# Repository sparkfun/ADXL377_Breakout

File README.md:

ADXL377 Breakout
================

[   
*Triple Axis Accelerometer Breakout-ADXL377 (SEN-12803)*](https://www.sparkfun.com/products/12803)

A Breakout Board for the ADXL377 Low Power 3-Axis ±200g Accelerometer with Analog Output.

Repository Contents
-------------------
* **/Hardware** - All Eagle design files (.brd, .sch)
* **/Production** - Test bed files and production panel files
* **/Firmware** - All Arduino sketches for this product

License Information
-------------------
The hardware is released under [Creative Commons ShareAlike 4.0 International](https://creativecommons.org/licenses/by-sa/4.0/).

Distributed as-is; no warranty is given.

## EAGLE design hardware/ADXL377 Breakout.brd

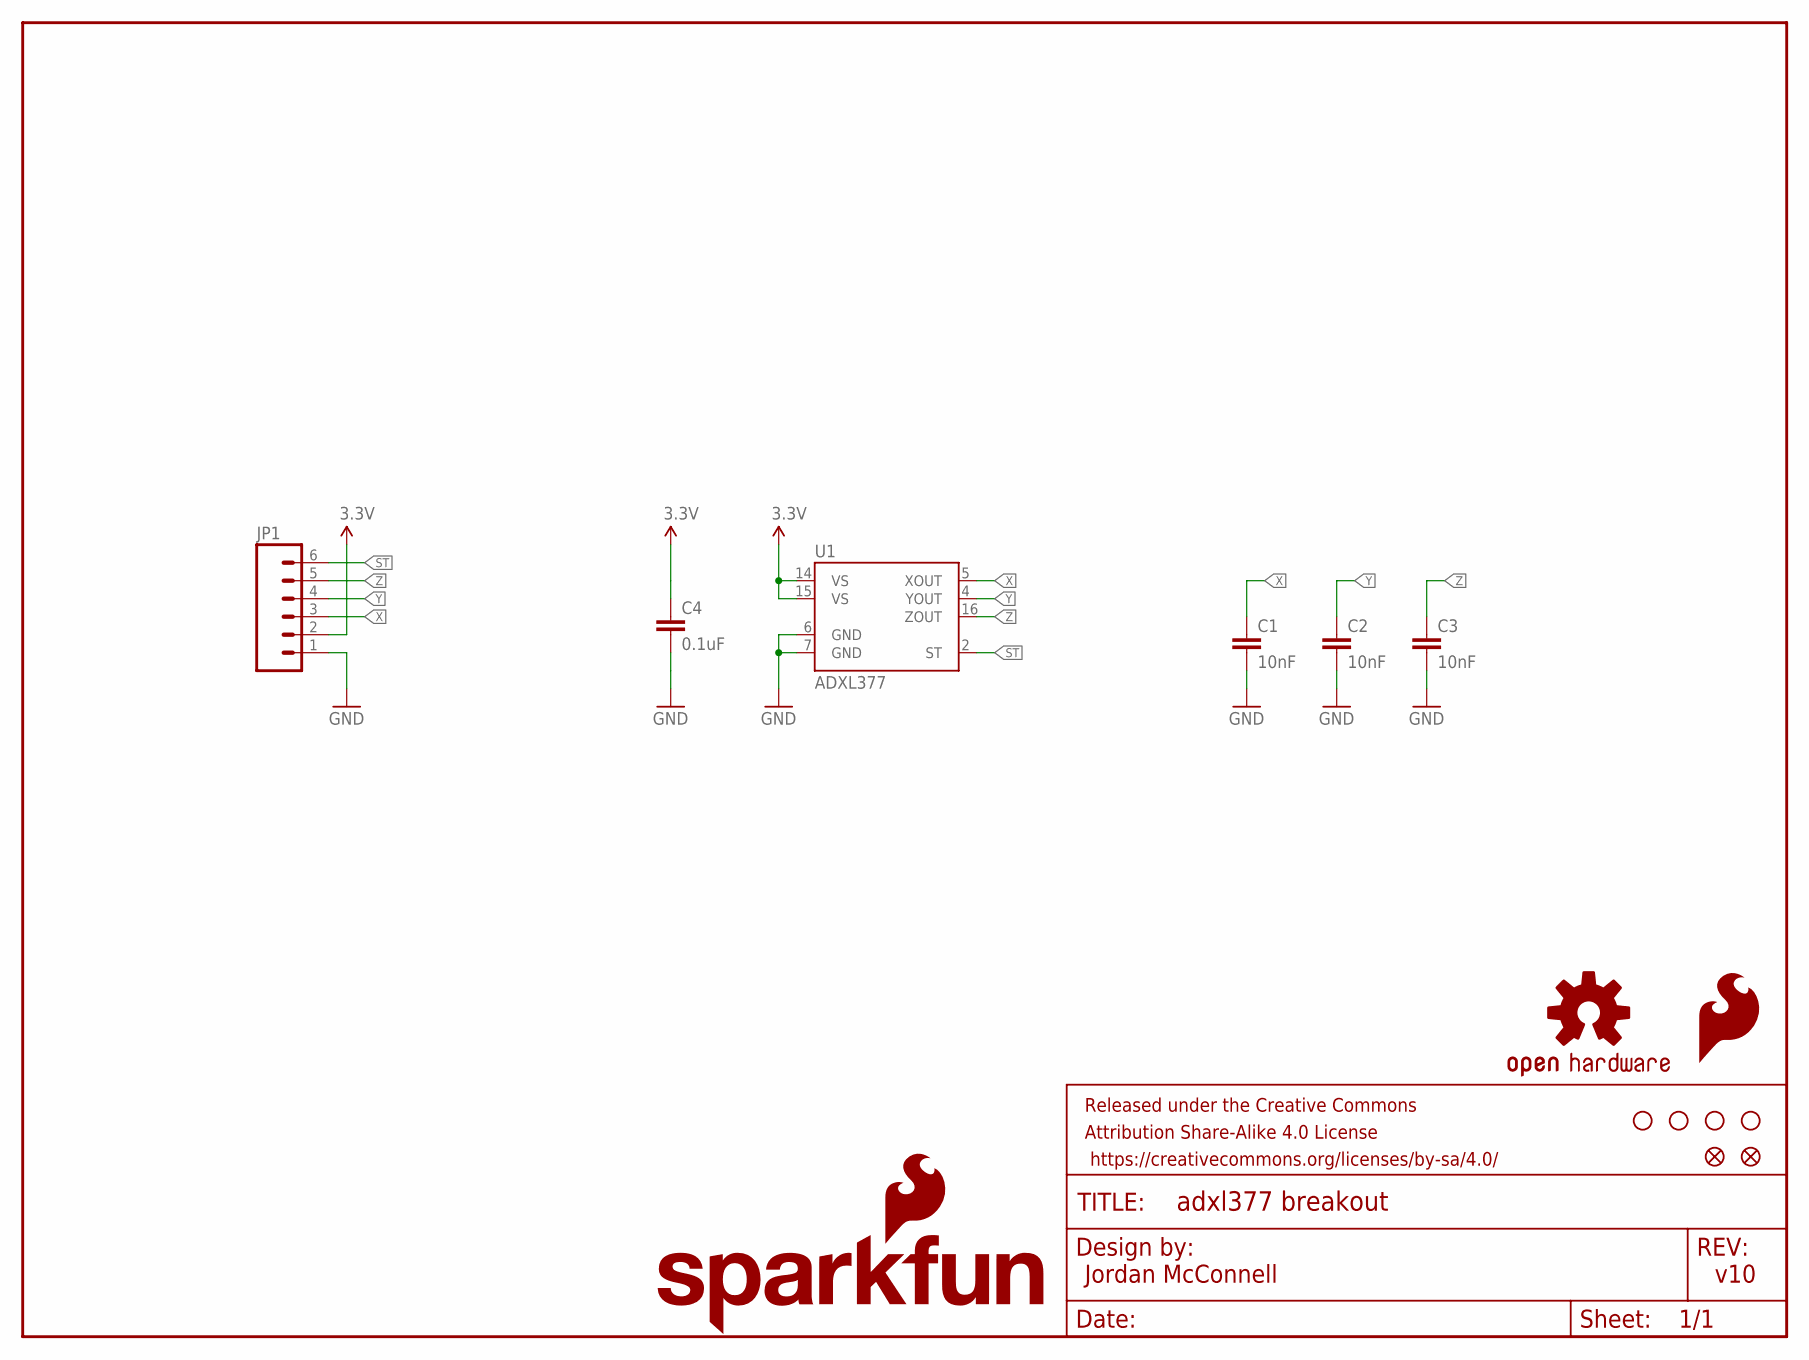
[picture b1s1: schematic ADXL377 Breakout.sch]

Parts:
C1, C2, C3: 10nF; 0603-CAP
C4: 0.1uF; 0603-CAP
FID1, FID2: FIDUCIAL1X2; FIDUCIAL-1X2
FRAME1: FRAME-LETTER; CREATIVE_COMMONS
JP1: M06SIP; 1X06
LOGO1: SFE_LOGO_FLAME.1_INCH; SFE_LOGO_FLAME_.1
LOGO2: OSHW-LOGOS; OSHW-LOGO-S
LOGO5: SFE_LOGO_NAME_FLAME.1_INCH; SFE_LOGO_NAME_FLAME_.1
STANDOFF1, STANDOFF2, STANDOFF3, STANDOFF4: STAND-OFF
U1: ADXL377; LFCSP_LQ-16

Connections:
3.3V: C4.1, JP1.2, U1.14 (VS), U1.15 (VS)
GND: C1.2, C2.2, C3.2, C4.2, JP1.1, U1.6 (GND), U1.7 (GND)
ST: JP1.6, U1.2 (ST)
X: C1.1, JP1.3, U1.5 (XOUT)
Y: C2.1, JP1.4, U1.4 (YOUT)
Z: C3.1, JP1.5, U1.16 (ZOUT)

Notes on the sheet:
Jordan McConnell
v10

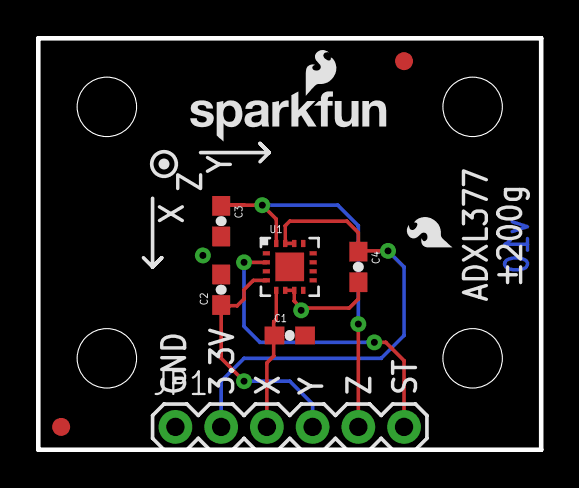
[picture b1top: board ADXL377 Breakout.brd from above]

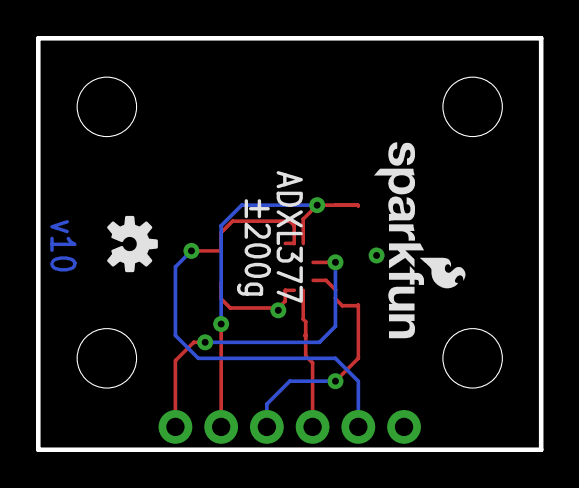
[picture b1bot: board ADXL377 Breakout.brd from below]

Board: 2 copper layers, 27.9 x 22.9 mm, 17 parts (2 on the bottom side), 6 nets.

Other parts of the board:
LOGO3: SFE_LOGO_NAME_FLAME.1_INCH; SFE_LOGO_NAME_FLAME_.1

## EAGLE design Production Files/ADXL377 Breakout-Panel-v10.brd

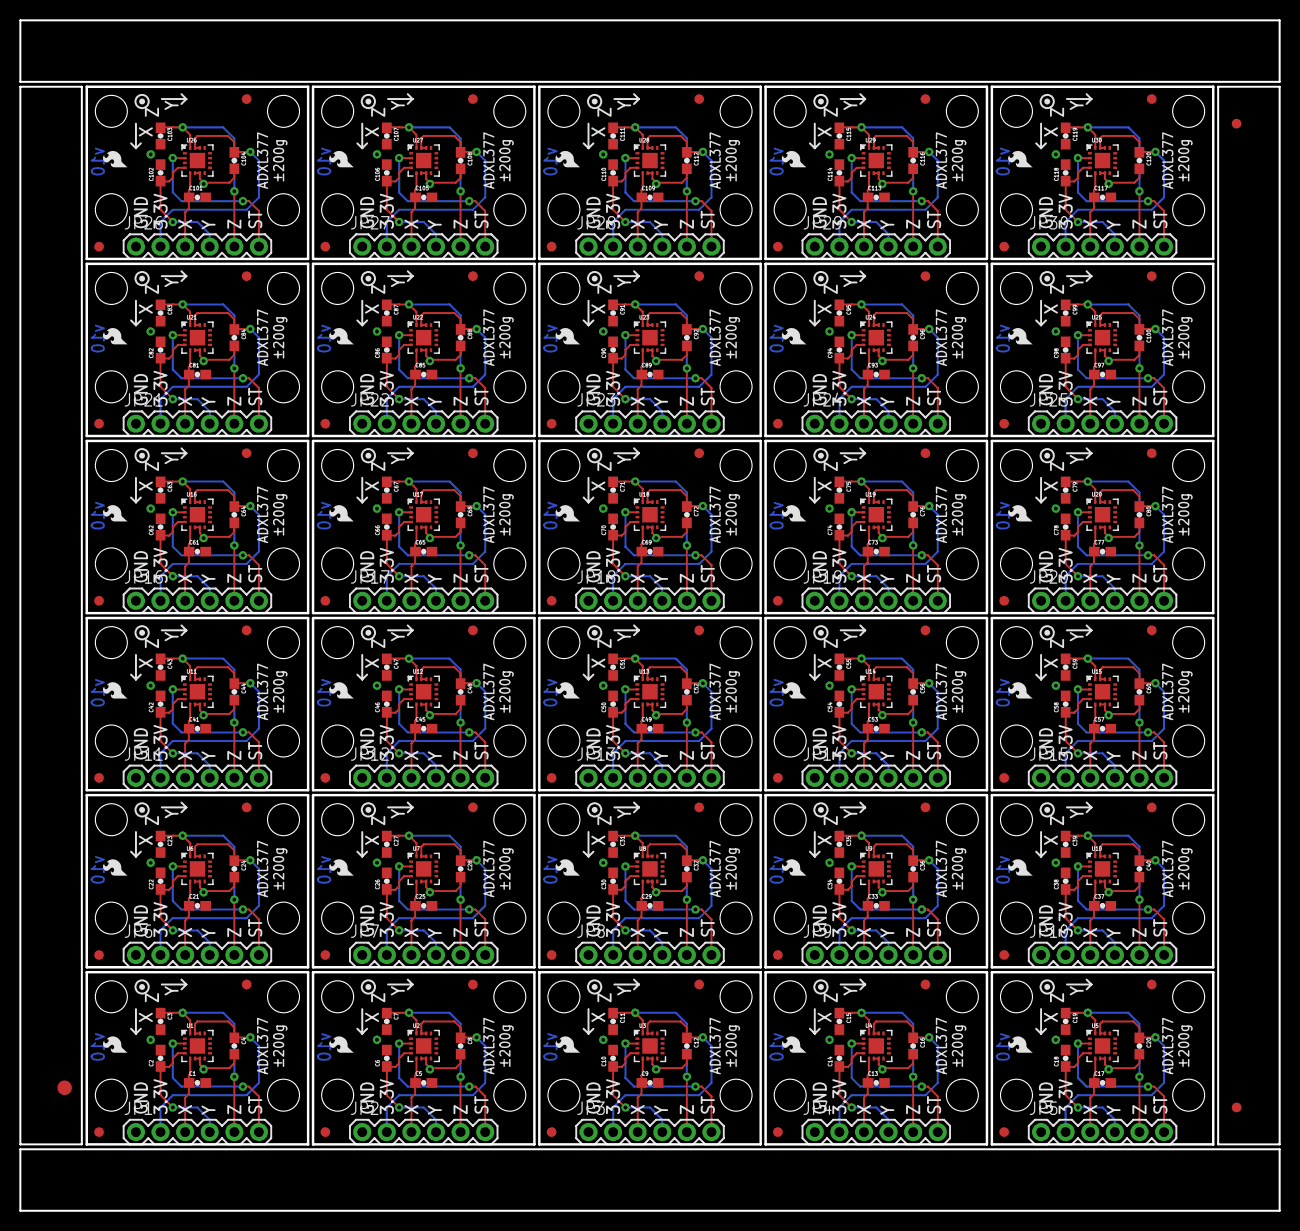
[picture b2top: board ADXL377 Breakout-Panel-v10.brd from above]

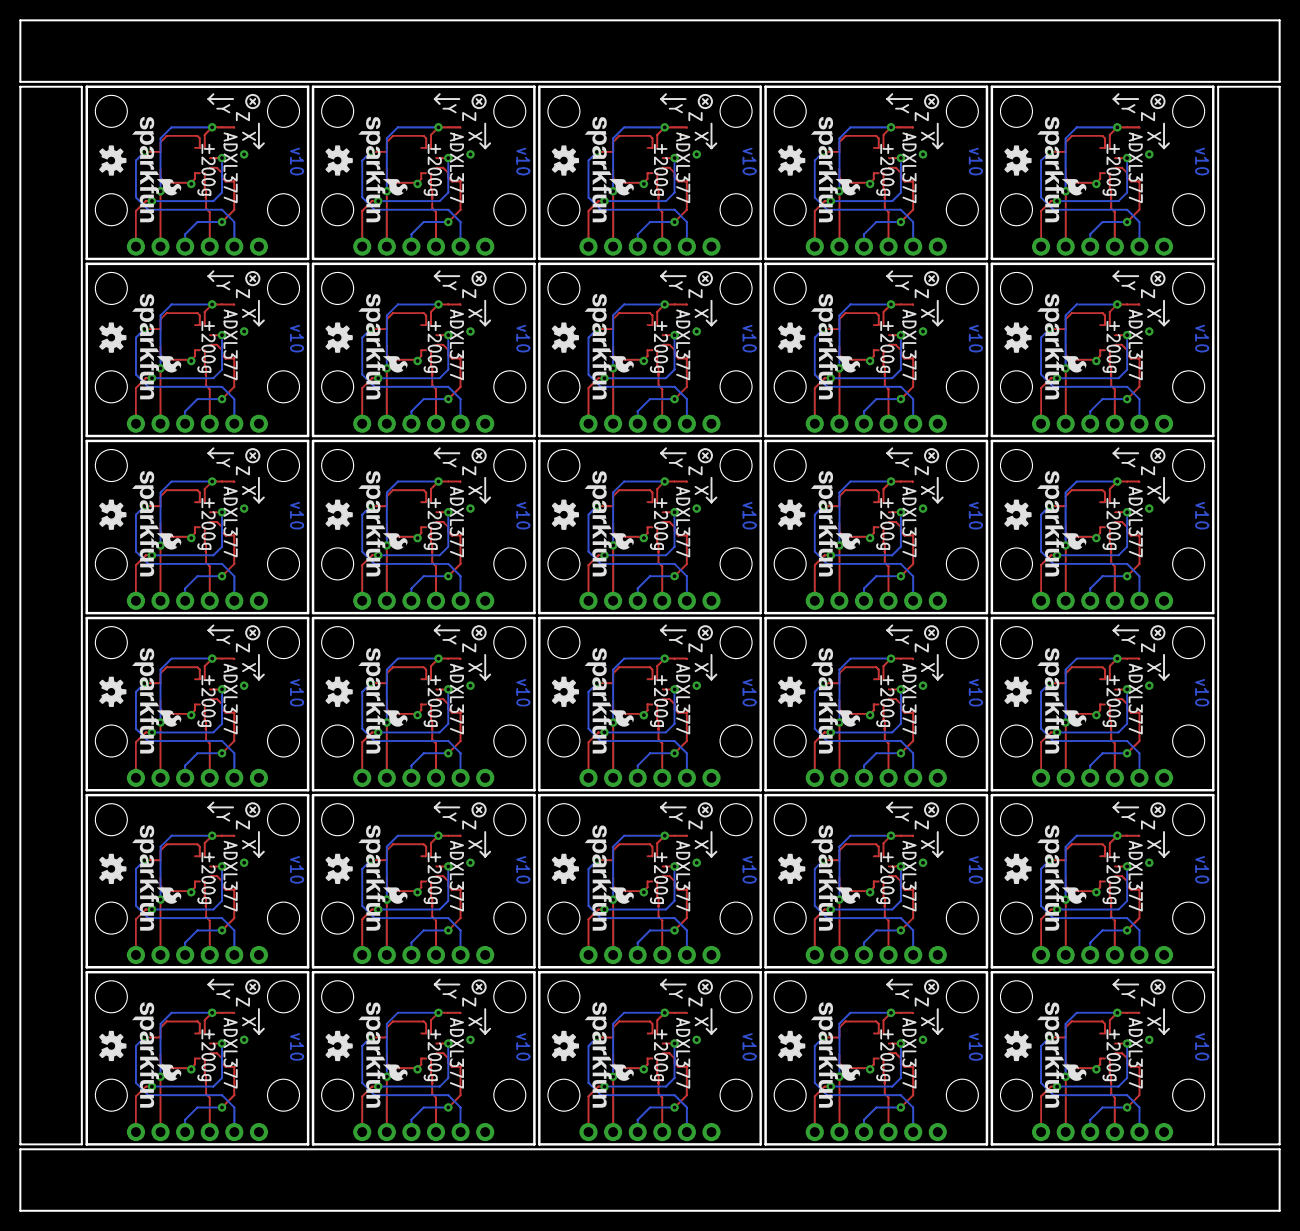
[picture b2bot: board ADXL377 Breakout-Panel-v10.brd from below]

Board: 2 copper layers, 130.0 x 122.9 mm, 453 parts (60 on the bottom side), 180 nets.

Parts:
C1, C2, C3, C5, C6, C7, C9, C10, C11, C13, C14, C15, C17, C18, C19, C21, C22, C23, C25, C26, C27, C29, C30, C31, C33, C34, C35, C37, C38, C39, C41, C42, C43, C45, C46, C47, C49, C50, C51, C53, C54, C55, C57, C58, C59, C61, C62, C63, C65, C66, C67, C69, C70, C71, C73, C74, C75, C77, C78, C79, C81, C82, C83, C85, C86, C87, C89, C90, C91, C93, C94, C95, C97, C98, C99, C101, C102, C103, C105, C106, C107, C109, C110, C111, C113, C114, C115, C117, C118, C119: 10nF; 0603-CAP
C4, C8, C12, C16, C20, C24, C28, C32, C36, C40, C44, C48, C52, C56, C60, C64, C68, C72, C76, C80, C84, C88, C92, C96, C100, C104, C108, C112, C116, C120: 0.1uF; 0603-CAP
E$1: FIDUCIAL-1.5X3
E$4, E$6: FIDUCIAL-1X2
FID1, FID2, FID3, FID4, FID5, FID6, FID7, FID8, FID9, FID10, FID11, FID12, FID13, FID14, FID15, FID16, FID17, FID18, FID19, FID20, FID21, FID22, FID23, FID24, FID25, FID26, FID27, FID28, FID29, FID30, FID31, FID32, FID33, FID34, FID35, FID36, FID37, FID38, FID39, FID40, FID41, FID42, FID43, FID44, FID45, FID46, FID47, FID48, FID49, FID50, FID51, FID52, FID53, FID54, FID55, FID56, FID57, FID58, FID59, FID60: FIDUCIAL1X2; FIDUCIAL-1X2
JP1, JP2, JP3, JP4, JP5, JP6, JP7, JP8, JP9, JP10, JP11, JP12, JP13, JP14, JP15, JP16, JP17, JP18, JP19, JP20, JP21, JP22, JP23, JP24, JP25, JP26, JP27, JP28, JP29, JP30: 1X06
LOGO1, LOGO4, LOGO7, LOGO10, LOGO13, LOGO16, LOGO19, LOGO22, LOGO25, LOGO28, LOGO31, LOGO34, LOGO37, LOGO40, LOGO43, LOGO46, LOGO49, LOGO52, LOGO55, LOGO58, LOGO61, LOGO64, LOGO67, LOGO70, LOGO73, LOGO76, LOGO79, LOGO82, LOGO85, LOGO88: SFE_LOGO_FLAME.1_INCH; SFE_LOGO_FLAME_.1
LOGO2, LOGO5, LOGO8, LOGO11, LOGO14, LOGO17, LOGO20, LOGO23, LOGO26, LOGO29, LOGO32, LOGO35, LOGO38, LOGO41, LOGO44, LOGO47, LOGO50, LOGO53, LOGO56, LOGO59, LOGO62, LOGO65, LOGO68, LOGO71, LOGO74, LOGO77, LOGO80, LOGO83, LOGO86, LOGO89: OSHW-LOGOS; OSHW-LOGO-S
LOGO3, LOGO6, LOGO9, LOGO12, LOGO15, LOGO18, LOGO21, LOGO24, LOGO27, LOGO30, LOGO33, LOGO36, LOGO39, LOGO42, LOGO45, LOGO48, LOGO51, LOGO54, LOGO57, LOGO60, LOGO63, LOGO66, LOGO69, LOGO72, LOGO75, LOGO78, LOGO81, LOGO84, LOGO87, LOGO90: SFE_LOGO_NAME_FLAME.1_INCH; SFE_LOGO_NAME_FLAME_.1
STANDOFF1, STANDOFF2, STANDOFF3, STANDOFF4, STANDOFF5, STANDOFF6, STANDOFF7, STANDOFF8, STANDOFF9, STANDOFF10, STANDOFF11, STANDOFF12, STANDOFF13, STANDOFF14, STANDOFF15, STANDOFF16, STANDOFF17, STANDOFF18, STANDOFF19, STANDOFF20, STANDOFF21, STANDOFF22, STANDOFF23, STANDOFF24, STANDOFF25, STANDOFF26, STANDOFF27, STANDOFF28, STANDOFF29, STANDOFF30, STANDOFF31, STANDOFF32, STANDOFF33, STANDOFF34, STANDOFF35, STANDOFF36, STANDOFF37, STANDOFF38, STANDOFF39, STANDOFF40, STANDOFF41, STANDOFF42, STANDOFF43, STANDOFF44, STANDOFF45, STANDOFF46, STANDOFF47, STANDOFF48, STANDOFF49, STANDOFF50, STANDOFF51, STANDOFF52, STANDOFF53, STANDOFF54, STANDOFF55, STANDOFF56, STANDOFF57, STANDOFF58, STANDOFF59, STANDOFF60, STANDOFF61, STANDOFF62, STANDOFF63, STANDOFF64, STANDOFF65, STANDOFF66, STANDOFF67, STANDOFF68, STANDOFF69, STANDOFF70, STANDOFF71, STANDOFF72, STANDOFF73, STANDOFF74, STANDOFF75, STANDOFF76, STANDOFF77, STANDOFF78, STANDOFF79, STANDOFF80, STANDOFF81, STANDOFF82, STANDOFF83, STANDOFF84, STANDOFF85, STANDOFF86, STANDOFF87, STANDOFF88, STANDOFF89, STANDOFF90, STANDOFF91, STANDOFF92, STANDOFF93, STANDOFF94, STANDOFF95, STANDOFF96, STANDOFF97, STANDOFF98, STANDOFF99, STANDOFF100, STANDOFF101, STANDOFF102, STANDOFF103, STANDOFF104, STANDOFF105, STANDOFF106, STANDOFF107, STANDOFF108, STANDOFF109, STANDOFF110, STANDOFF111, STANDOFF112, STANDOFF113, STANDOFF114, STANDOFF115, STANDOFF116, STANDOFF117, STANDOFF118, STANDOFF119, STANDOFF120: STAND-OFF
U1, U2, U3, U4, U5, U6, U7, U8, U9, U10, U11, U12, U13, U14, U15, U16, U17, U18, U19, U20, U21, U22, U23, U24, U25, U26, U27, U28, U29, U30: ADXL377; LFCSP_LQ-16

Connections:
3.3V: C4.1, JP1.2, U1.14, U1.15
3.3V1: C8.1, JP2.2, U2.14, U2.15
3.3V2: C12.1, JP3.2, U3.14, U3.15
3.3V3: C16.1, JP4.2, U4.14, U4.15
3.3V4: C20.1, JP5.2, U5.14, U5.15
3.3V5: C24.1, JP6.2, U6.14, U6.15
3.3V6: C28.1, JP7.2, U7.14, U7.15
3.3V7: C32.1, JP8.2, U8.14, U8.15
3.3V8: C36.1, JP9.2, U9.14, U9.15
3.3V9: C40.1, JP10.2, U10.14, U10.15
3.3V10: C44.1, JP11.2, U11.14, U11.15
3.3V11: C48.1, JP12.2, U12.14, U12.15
3.3V12: C52.1, JP13.2, U13.14, U13.15
3.3V13: C56.1, JP14.2, U14.14, U14.15
3.3V14: C60.1, JP15.2, U15.14, U15.15
3.3V15: C64.1, JP16.2, U16.14, U16.15
3.3V16: C68.1, JP17.2, U17.14, U17.15
3.3V17: C72.1, JP18.2, U18.14, U18.15
3.3V18: C76.1, JP19.2, U19.14, U19.15
3.3V19: C80.1, JP20.2, U20.14, U20.15
3.3V20: C84.1, JP21.2, U21.14, U21.15
3.3V21: C88.1, JP22.2, U22.14, U22.15
3.3V22: C92.1, JP23.2, U23.14, U23.15
3.3V23: C96.1, JP24.2, U24.14, U24.15
3.3V24: C100.1, JP25.2, U25.14, U25.15
3.3V25: C104.1, JP26.2, U26.14, U26.15
3.3V26: C108.1, JP27.2, U27.14, U27.15
3.3V27: C112.1, JP28.2, U28.14, U28.15
3.3V28: C116.1, JP29.2, U29.14, U29.15
3.3V29: C120.1, JP30.2, U30.14, U30.15
GND: C1.2, C2.2, C3.2, C4.2, JP1.1, U1.6, U1.7
GND1: C5.2, C6.2, C7.2, C8.2, JP2.1, U2.6, U2.7
GND2: C9.2, C10.2, C11.2, C12.2, JP3.1, U3.6, U3.7
GND3: C13.2, C14.2, C15.2, C16.2, JP4.1, U4.6, U4.7
GND4: C17.2, C18.2, C19.2, C20.2, JP5.1, U5.6, U5.7
GND5: C21.2, C22.2, C23.2, C24.2, JP6.1, U6.6, U6.7
GND6: C25.2, C26.2, C27.2, C28.2, JP7.1, U7.6, U7.7
GND7: C29.2, C30.2, C31.2, C32.2, JP8.1, U8.6, U8.7
GND8: C33.2, C34.2, C35.2, C36.2, JP9.1, U9.6, U9.7
GND9: C37.2, C38.2, C39.2, C40.2, JP10.1, U10.6, U10.7
GND10: C41.2, C42.2, C43.2, C44.2, JP11.1, U11.6, U11.7
GND11: C45.2, C46.2, C47.2, C48.2, JP12.1, U12.6, U12.7
GND12: C49.2, C50.2, C51.2, C52.2, JP13.1, U13.6, U13.7
GND13: C53.2, C54.2, C55.2, C56.2, JP14.1, U14.6, U14.7
GND14: C57.2, C58.2, C59.2, C60.2, JP15.1, U15.6, U15.7
GND15: C61.2, C62.2, C63.2, C64.2, JP16.1, U16.6, U16.7
GND16: C65.2, C66.2, C67.2, C68.2, JP17.1, U17.6, U17.7
GND17: C69.2, C70.2, C71.2, C72.2, JP18.1, U18.6, U18.7
GND18: C73.2, C74.2, C75.2, C76.2, JP19.1, U19.6, U19.7
GND19: C77.2, C78.2, C79.2, C80.2, JP20.1, U20.6, U20.7
GND20: C81.2, C82.2, C83.2, C84.2, JP21.1, U21.6, U21.7
GND21: C85.2, C86.2, C87.2, C88.2, JP22.1, U22.6, U22.7
GND22: C89.2, C90.2, C91.2, C92.2, JP23.1, U23.6, U23.7
GND23: C93.2, C94.2, C95.2, C96.2, JP24.1, U24.6, U24.7
GND24: C97.2, C98.2, C99.2, C100.2, JP25.1, U25.6, U25.7
GND25: C101.2, C102.2, C103.2, C104.2, JP26.1, U26.6, U26.7
GND26: C105.2, C106.2, C107.2, C108.2, JP27.1, U27.6, U27.7
GND27: C109.2, C110.2, C111.2, C112.2, JP28.1, U28.6, U28.7
GND28: C113.2, C114.2, C115.2, C116.2, JP29.1, U29.6, U29.7
GND29: C117.2, C118.2, C119.2, C120.2, JP30.1, U30.6, U30.7
ST: JP1.6, U1.2
ST1: JP2.6, U2.2
ST2: JP3.6, U3.2
ST3: JP4.6, U4.2
ST4: JP5.6, U5.2
ST5: JP6.6, U6.2
ST6: JP7.6, U7.2
ST7: JP8.6, U8.2
ST8: JP9.6, U9.2
ST9: JP10.6, U10.2
ST10: JP11.6, U11.2
ST11: JP12.6, U12.2
ST12: JP13.6, U13.2
ST13: JP14.6, U14.2
ST14: JP15.6, U15.2
ST15: JP16.6, U16.2
ST16: JP17.6, U17.2
ST17: JP18.6, U18.2
ST18: JP19.6, U19.2
ST19: JP20.6, U20.2
ST20: JP21.6, U21.2
ST21: JP22.6, U22.2
ST22: JP23.6, U23.2
ST23: JP24.6, U24.2
ST24: JP25.6, U25.2
ST25: JP26.6, U26.2
ST26: JP27.6, U27.2
ST27: JP28.6, U28.2
ST28: JP29.6, U29.2
ST29: JP30.6, U30.2
X: C1.1, JP1.3, U1.5
X1: C5.1, JP2.3, U2.5
X2: C9.1, JP3.3, U3.5
X3: C13.1, JP4.3, U4.5
X4: C17.1, JP5.3, U5.5
X5: C21.1, JP6.3, U6.5
X6: C25.1, JP7.3, U7.5
X7: C29.1, JP8.3, U8.5
X8: C33.1, JP9.3, U9.5
X9: C37.1, JP10.3, U10.5
X10: C41.1, JP11.3, U11.5
X11: C45.1, JP12.3, U12.5
X12: C49.1, JP13.3, U13.5
X13: C53.1, JP14.3, U14.5
X14: C57.1, JP15.3, U15.5
X15: C61.1, JP16.3, U16.5
X16: C65.1, JP17.3, U17.5
X17: C69.1, JP18.3, U18.5
X18: C73.1, JP19.3, U19.5
X19: C77.1, JP20.3, U20.5
X20: C81.1, JP21.3, U21.5
X21: C85.1, JP22.3, U22.5
X22: C89.1, JP23.3, U23.5
X23: C93.1, JP24.3, U24.5
X24: C97.1, JP25.3, U25.5
X25: C101.1, JP26.3, U26.5
X26: C105.1, JP27.3, U27.5
X27: C109.1, JP28.3, U28.5
X28: C113.1, JP29.3, U29.5
X29: C117.1, JP30.3, U30.5
Y: C2.1, JP1.4, U1.4
Y1: C6.1, JP2.4, U2.4
Y2: C10.1, JP3.4, U3.4
Y3: C14.1, JP4.4, U4.4
Y4: C18.1, JP5.4, U5.4
Y5: C22.1, JP6.4, U6.4
Y6: C26.1, JP7.4, U7.4
Y7: C30.1, JP8.4, U8.4
Y8: C34.1, JP9.4, U9.4
Y9: C38.1, JP10.4, U10.4
Y10: C42.1, JP11.4, U11.4
Y11: C46.1, JP12.4, U12.4
Y12: C50.1, JP13.4, U13.4
Y13: C54.1, JP14.4, U14.4
Y14: C58.1, JP15.4, U15.4
Y15: C62.1, JP16.4, U16.4
Y16: C66.1, JP17.4, U17.4
Y17: C70.1, JP18.4, U18.4
Y18: C74.1, JP19.4, U19.4
Y19: C78.1, JP20.4, U20.4
Y20: C82.1, JP21.4, U21.4
Y21: C86.1, JP22.4, U22.4
Y22: C90.1, JP23.4, U23.4
Y23: C94.1, JP24.4, U24.4
Y24: C98.1, JP25.4, U25.4
Y25: C102.1, JP26.4, U26.4
Y26: C106.1, JP27.4, U27.4
Y27: C110.1, JP28.4, U28.4
Y28: C114.1, JP29.4, U29.4
Y29: C118.1, JP30.4, U30.4
Z: C3.1, JP1.5, U1.16
Z1: C7.1, JP2.5, U2.16
Z2: C11.1, JP3.5, U3.16
Z3: C15.1, JP4.5, U4.16
Z4: C19.1, JP5.5, U5.16
Z5: C23.1, JP6.5, U6.16
Z6: C27.1, JP7.5, U7.16
Z7: C31.1, JP8.5, U8.16
Z8: C35.1, JP9.5, U9.16
Z9: C39.1, JP10.5, U10.16
Z10: C43.1, JP11.5, U11.16
Z11: C47.1, JP12.5, U12.16
Z12: C51.1, JP13.5, U13.16
Z13: C55.1, JP14.5, U14.16
Z14: C59.1, JP15.5, U15.16
Z15: C63.1, JP16.5, U16.16
Z16: C67.1, JP17.5, U17.16
Z17: C71.1, JP18.5, U18.16
Z18: C75.1, JP19.5, U19.16
Z19: C79.1, JP20.5, U20.16
Z20: C83.1, JP21.5, U21.16
Z21: C87.1, JP22.5, U22.16
Z22: C91.1, JP23.5, U23.16
Z23: C95.1, JP24.5, U24.16
Z24: C99.1, JP25.5, U25.16
Z25: C103.1, JP26.5, U26.16
Z26: C107.1, JP27.5, U27.16
Z27: C111.1, JP28.5, U28.16
Z28: C115.1, JP29.5, U29.16
Z29: C119.1, JP30.5, U30.16

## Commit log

2014-03-06 v01 ready for review
2014-03-10 Added 4 mounting holes and modified silk, ready for protos
2014-03-13 made slight board adjustment, v01 ready for protos
2014-05-16 v10 ready for review
2014-05-20 v10, ready for reds
2014-05-27 created panel v10
2014-07-15 Added Arduino example sketch
2014-07-16 Added product photo/info to readme

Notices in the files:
parts and their libraries:
SparkFun-Aesthetics: Licensing: Creative Commons ShareAlike 4.0 International - https://creativecommons.org/licenses/by-sa/4.0
SparkFun-Aesthetics: Released under the Creative Commons Attribution Share-Alike 4.0 License
SparkFun-Aesthetics: Released under the Creative Commons
